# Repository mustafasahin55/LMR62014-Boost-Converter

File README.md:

# LMR62014 Boost Converter

This project involves a Texas Instruments LMR62014 DC-DC boost converter circuit, designed to step up a low DC input voltage to a higher DC output voltage. This type of circuit is especially useful in low-power electronics, battery-powered systems, and various industrial applications.

## Features
- Input Voltage: 2.7V - 14V
- Output Voltage: 12V
- Maximum Output Current: Supports up to 0.5A
- High Efficiency: Efficiency over 93%, ensuring minimal energy loss

## Circuit Schematic
The circuit schematic and detailed component list can be found in the [schematic](https://github.com/mustafasahin55/LMR62014-Boost-Converter/blob/main/Schematic.pdf) file. Refer to this file to assemble the circuit accurately.

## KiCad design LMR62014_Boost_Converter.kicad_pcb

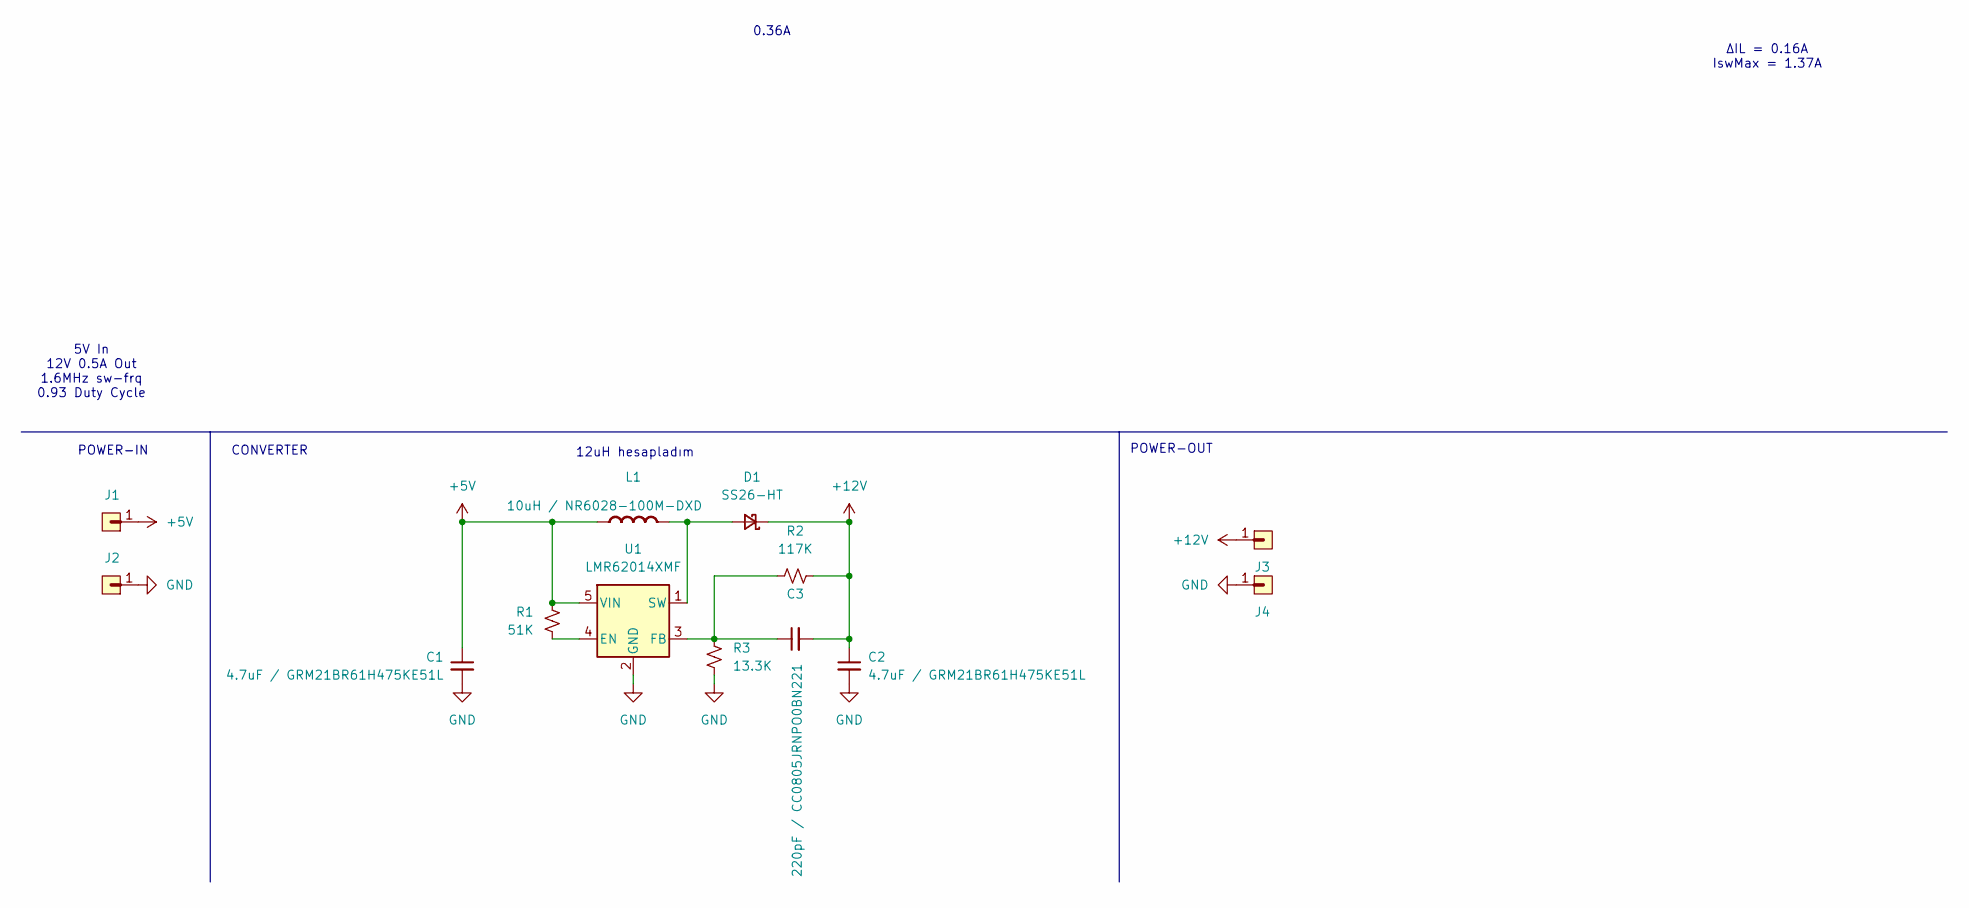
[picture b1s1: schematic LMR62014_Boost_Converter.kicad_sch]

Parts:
C1, C2: 4.7uF / GRM21BR61H475KE51L; C_0805_2012Metric
C3: 220pF / CC0805JRNPO0BN221; C_0805_2012Metric
D1: SS26-HT; D_SMA-SMB_Universal_Handsoldering
J1: 5V_In; PinHeader_1x01_P2.54mm_Vertical
J2: GND_In; PinHeader_1x01_P2.54mm_Vertical
J3: 12V_OUT; PinHeader_1x01_P2.54mm_Vertical
J4: GND_OUT; PinHeader_1x01_P2.54mm_Vertical
L1: 10uH / NR6028-100M-DXD; L_Changjiang_FNR6028S; Rating A
R1: 51K; R_0805_2012Metric
R2: 117K; R_0805_2012Metric
R3: 13.3K; R_0805_2012Metric
U1: LMR62014XMF; SOT-23-5

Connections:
+5V: C1.1, J1.1, L1.1 (+), R1.2, U1.5 (VIN)
+12V: C2.1, C3.2, D1.1 (K), J3.1, R2.1
GND: C1.2, C2.2, J2.1, J4.1, R3.2, U1.2 (GND)
unnamed: D1.2 (A), L1.2 (-), U1.1 (SW)
unnamed: R1.1, U1.4 (EN)
unnamed: C3.1, R2.2, R3.1, U1.3 (FB)

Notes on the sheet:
5V In 12V 0.5A Out 1.6MHz sw-frq 0.93 Duty Cycle
12uH hesapladım
CONVERTER
POWER-IN
POWER-OUT
0.36A
ΔIL = 0.16A IswMax = 1.37A

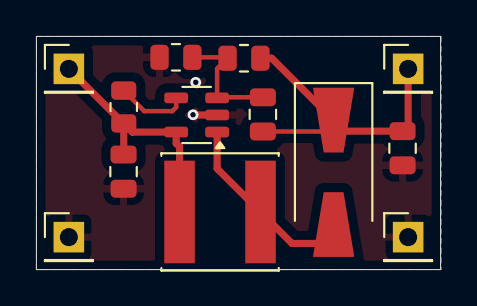
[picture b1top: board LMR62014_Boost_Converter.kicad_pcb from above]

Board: 2 copper layers, 22.5 x 13.0 mm, 13 parts (0 on the bottom side), 6 nets.

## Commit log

2024-10-31 v1.0
    first commit
